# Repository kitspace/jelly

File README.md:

# Light-following Jellyfish Bristlebot

This is a small light following robot that consists of a simple analog circuit and uses pager vibration motors and toothbrush heads as a form of locomotion. 
This was heavily inspired by [Facelesstech's project](https://facelesstech.wordpress.com/2016/08/15/light-following-bristle-bot/) but adds jellyfishness (with the help of [svg2mod](https://github.com/mtl/svg2mod)).

## Parts
You can buy most of the parts through the [Kitspace page](https://kitspace.org/jelly) but you will also need:

- 2 toothbrush heads (use some old ones!)
- A LiPo battery with a JST connector and built-in protection, anything between 200 - 400mAh should work well (e.g. [from Adafruit](https://www.adafruit.com/product/2750))
- 2 pager vibration motors (e.g. [from Amazon](https://www.amazon.co.uk/Vibration-Motor-TOOGOO-4-6mm-2000RPM/dp/B01H01PXQ2))
- 3 100mm cable ties (e.g. [from Amazon](https://www.amazon.co.uk/Sealey-CT25101-Cable-Ties-100mm/dp/B000RO146I))

## Instructions

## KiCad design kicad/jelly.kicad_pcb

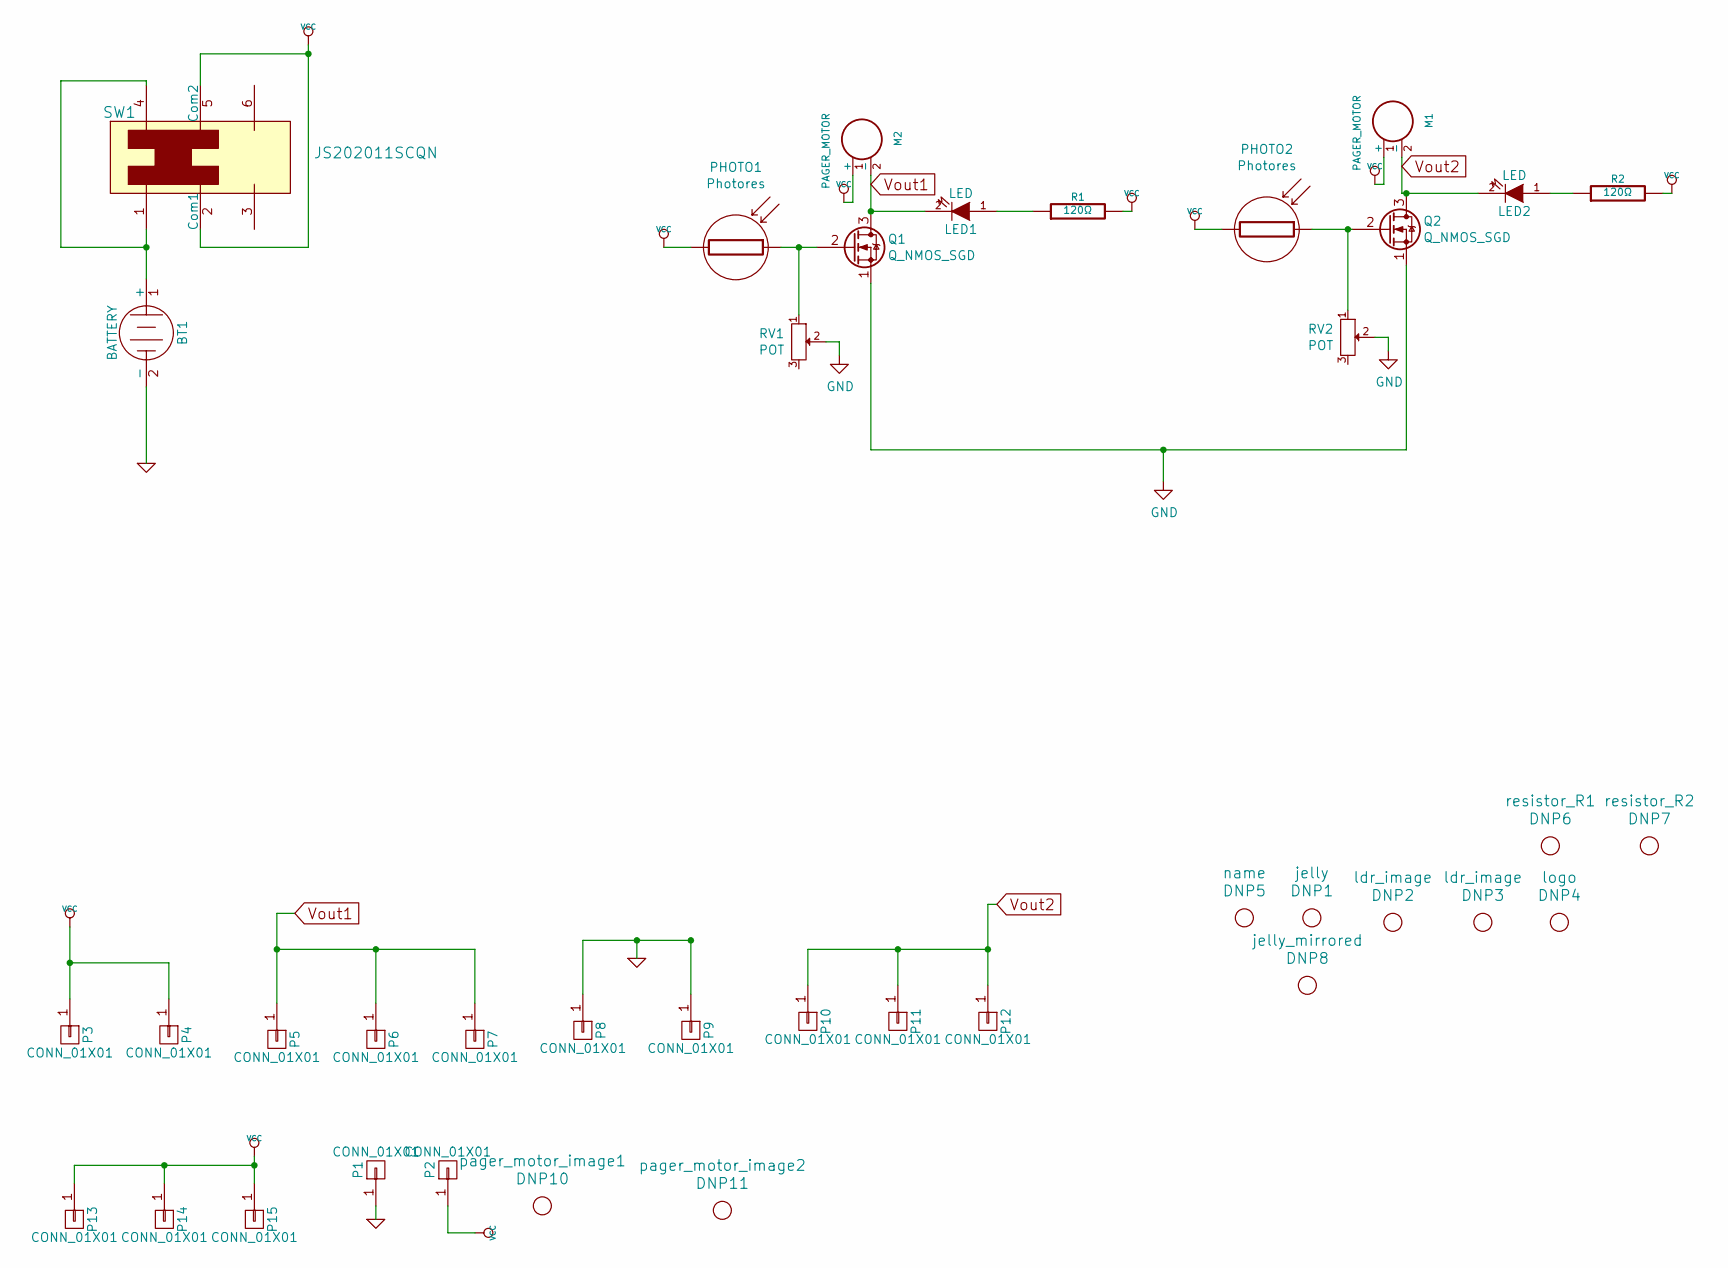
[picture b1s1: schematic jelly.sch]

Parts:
BT1: BATTERY; JST_PH_S2B-PH-K_02x2.00mm_Angled
DNP1: jelly
DNP2: ldr_image
DNP3: ldr_image; ldr_image_flipped
DNP4: logo
DNP5: name
DNP6: resistor_R1; resistor
DNP7: resistor_R2; resistor
DNP8: jelly_mirrored
DNP10: pager_motor_image1; page_motor_image
DNP11: pager_motor_image2; page_motor_image_flipped
LED1, LED2: LED; LED-5MM; Farnell 2112111
M1, M2: PAGER_MOTOR; pager_motor_custom
P1, P2: CONN_01X01; hole
P3, P4, P5, P6, P7, P8, P9, P10, P11, P12, P13, P14, P15: CONN_01X01; hole2
PHOTO1, PHOTO2: Photores; ldr
Q1: Q_NMOS_SGD; TO-92_Inline_Narrow_Oval; Farnell 9845178
Q2: Q_NMOS_SGD; TO-92_Inline_Narrow_Oval
R1, R2: 120Ω; R3-5
RV1, RV2: POT; Potentiometer_Triwood_RM-065; Farnell 8867046
SW1: JS202011SCQN; MPN JS202011SCQN; Digi-Key_PN 401-2002-1-ND

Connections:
GND: BT1.2 (-), P1.1, P8.1, P9.1, Q1.1 (S), Q2.1 (S), RV1.2, RV2.2
unnamed: BT1.1 (+), SW1.1, SW1.4
unnamed: LED1.1 (A), R1.1
unnamed: LED2.1 (A), R2.1
unnamed: PHOTO1.1, Q1.2 (G), RV1.1
unnamed: PHOTO2.1, Q2.2 (G), RV2.1
VCC: M1.1 (+), M2.1 (+), P2.1, P3.1, P4.1, P13.1, P14.1, P15.1, PHOTO1.2, PHOTO2.2, R1.2, R2.2, SW1.2 (Com1), SW1.5 (Com2)
Vout1: LED1.2 (K), M2.2 (-), P5.1, P6.1, P7.1, Q1.3 (D)
Vout2: LED2.2 (K), M1.2 (-), P10.1, P11.1, P12.1, Q2.3 (D)

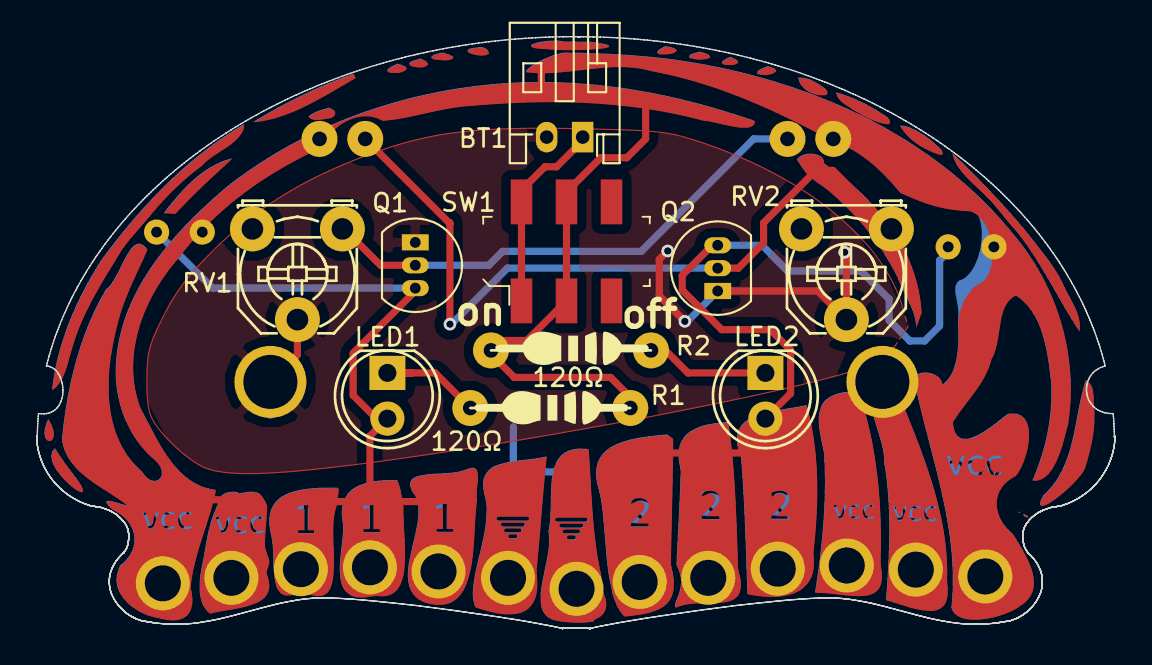
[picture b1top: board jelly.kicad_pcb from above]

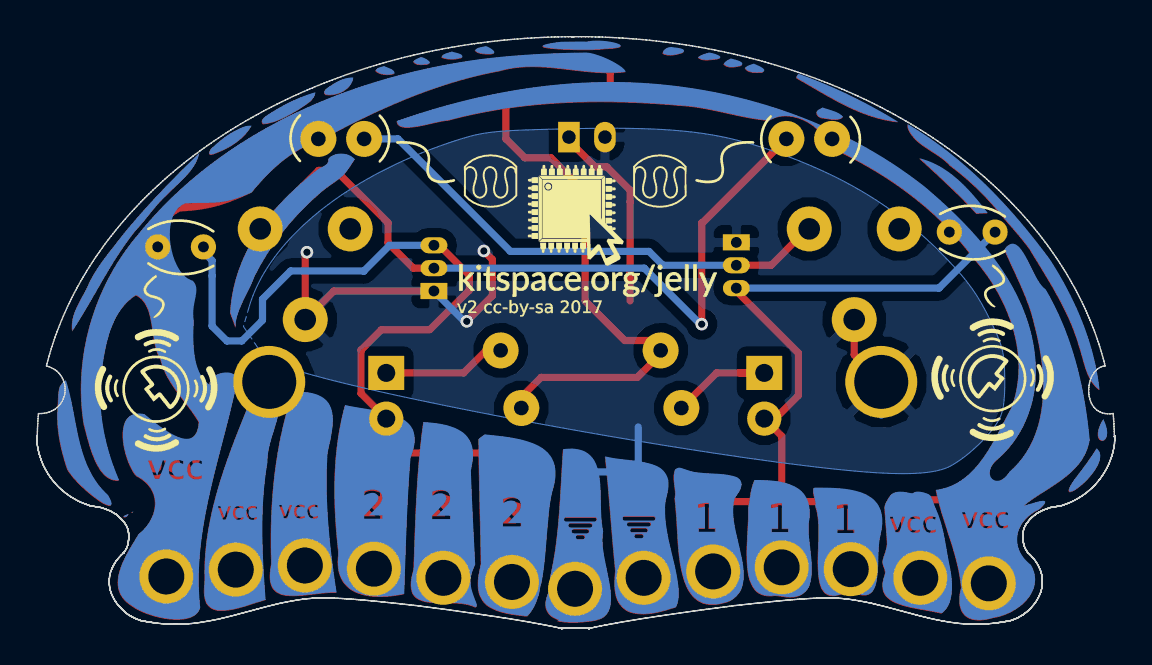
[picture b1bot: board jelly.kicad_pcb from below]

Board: 2 copper layers, 59.9 x 32.9 mm, 39 parts (5 on the bottom side), 9 nets.

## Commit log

2016-08-26 Work on jelly
2016-08-26 Work on jelly copper
2016-08-26 Adjust copper on jelly
2016-08-27 Add some components
2016-08-27 Add kitnic.yaml and 1-click-bom
2016-08-27 Convert svg with higher precision
2016-08-27 Make holes part of copper
2016-08-27 Remove holes from jelly pads
2016-08-27 Plot Gerbers
2016-08-27 Play with layout
2016-08-28 Layout some components
2016-08-28 Move things about
2016-08-28 Add .gitignore and clean up
2016-08-28 Re-plot gerbers
2016-08-28 Add LDR silkscreen image
2016-08-28 Re-arrange connector holes
2016-08-28 Add notches to outline and remove holes
2016-08-28 Adjust copper specks near edges
2016-08-28 Make room for motor pads
2016-08-28 Adjust position of right motor
2016-08-28 Play around with some routing
2016-08-28 Switch to CR2450 battery holder
2016-08-28 Try and fit things in around CR2450
    doesn't look possible
2016-08-28 Give up on CR2450
2016-09-28 Turn of visibility of footprint fields in schematic
2016-09-28 Add tilt switch and work out transistor choice
2016-09-28 Switch to low side switch and layout about
2016-10-08 Make jelly get out of the way
2016-10-08 Work on silkscreen and jelly
2016-10-08 Route
2016-10-08 Adjust traces and plot
2016-10-08 Remove values from plot
2016-10-08 Draw names on pads
2016-10-08 Work on pad names
2016-10-15 Work on jelly pad labels
2016-10-15 Add logo and name
2016-10-15 Start to replace jelly pad idents
2016-10-15 Use triangle labels
2016-10-15 Move labels down
2016-10-15 Make image for LDR silkscreen
2016-10-15 Add resistor silkscreen
2016-10-15 Re-plot
2016-10-15 Fix some traces
2016-10-15 Rename leds from D to LED
2016-10-15 Add page motor silkscreen image
2016-10-15 Adjust LDR silkscreen brackets
2016-10-15 Add plus and minus labels
2016-10-15 Move LDR drawings
2016-10-15 Move Q references
2016-10-15 Re-route
2016-10-16 Add mercury switch drawing
2016-10-16 Move jelly slightly out of the way
2016-10-16 Make sure footprints and schematic are in sync
2016-10-16 Adjust triangle labels
2016-10-16 Remove fills
2016-10-16 Use svg2mod to get a polygon for zone
2016-10-16 Adjust logo size
2016-10-16 Run DRC and plot
2016-10-16 Add version text
2016-10-16 Add creative commons logo
2016-10-16 Add copper zone cutout around cc logo
2016-10-16 Clear old values in BOM
2017-03-05 Make sure pcb can be opened in kicad stable
2017-03-05 Go through BOM
2017-03-05 Fix small mistakes in README
2017-03-05 Fix resistor selection and improve BOM
2017-03-05 Be clearer about quantities in README
2017-03-22 Add update to README
2017-05-25 Increase annular rings on quite a few pads
    fixes #2
2017-05-25 Switch to stable kicad and re-plot
2017-05-25 Add second motor and new main switch to simulation
2017-05-25 Update simulation
2017-05-25 Clean up BOM
2017-05-26 Start re-arranging layout
2017-11-27 Remove mercury switch
2017-11-28 Add new switch and battery connector
2017-11-28 Re-arrange some components
2017-11-28 Update jelly svg and netlist
2017-11-28 Add jelly drawing on the back
2017-11-28 Adjust jelly for pad
2017-11-28 Mirror jelly pad names
2017-11-28 Adjust silkscreen and plot
2017-11-28 Adjust silkscreen and start on instructions
2017-11-28 Add on/off to silkscreen near switch
2017-11-29 Add links to extra parts in README
2017-11-29 Update BOM
2017-11-29 Small fixes to README
2017-11-30 Fix motor connections
